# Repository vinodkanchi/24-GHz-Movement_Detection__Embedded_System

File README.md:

# 24-GHz-Movement_Detection__Embedded_System
The project is movement detection system where we design a PCB board for a Bandpass filter for allowing specific frequency using KiCad, then we do an embedded detection system using FreeSo-2, here we use ADC,DAC and LED's. Finally the next step is to test the model for the required frequency and gain measurements.

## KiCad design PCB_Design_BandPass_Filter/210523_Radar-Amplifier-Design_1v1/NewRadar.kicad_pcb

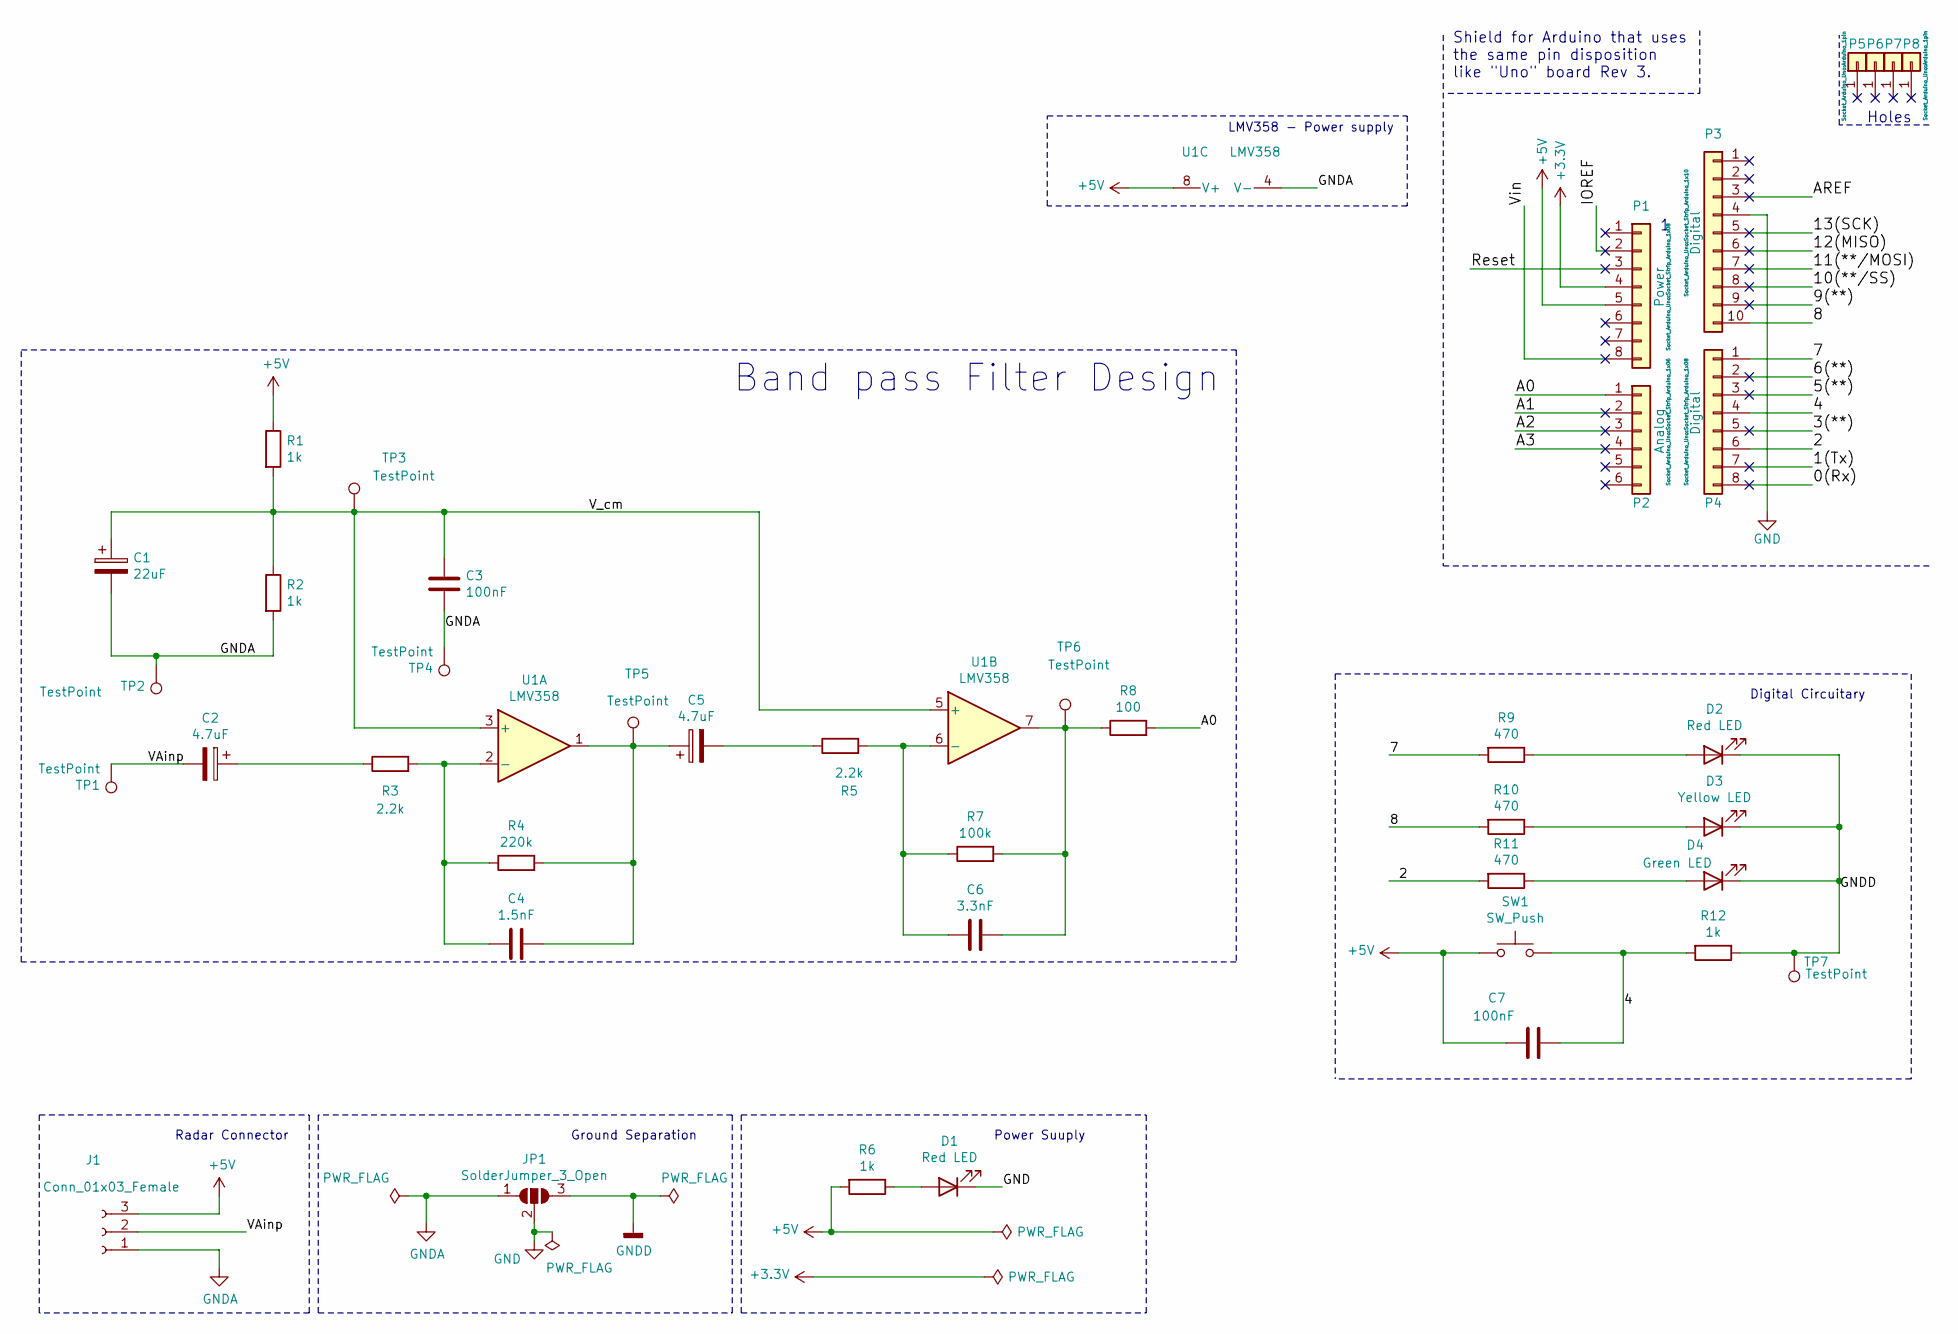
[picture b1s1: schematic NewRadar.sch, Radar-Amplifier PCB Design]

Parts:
C1: 22uF; C_Radial_D5.0mm_H11.0mm_P2.00mm
C2, C5: 4.7uF; C_Radial_D5.0mm_H11.0mm_P2.00mm
C3, C7: 100nF; C_Rect_L7.2mm_W2.5mm_P5.00mm_FKS2_FKP2_MKS2_MKP2
C4: 1.5nF; C_Rect_L7.2mm_W4.5mm_P5.00mm_FKS2_FKP2_MKS2_MKP2
C6: 3.3nF; C_Rect_L7.2mm_W4.5mm_P5.00mm_FKS2_FKP2_MKS2_MKP2
D1, D2: Red LED; LED_1206_3216Metric_Pad1.42x1.75mm_HandSolder
D3: Yellow LED; LED_1206_3216Metric_Pad1.42x1.75mm_HandSolder
D4: Green LED; LED_1206_3216Metric_Pad1.42x1.75mm_HandSolder
J1: Conn_01x03_Female; PinSocket_1x03_P2.54mm_Horizontal
JP1: SolderJumper_3_Open; SolderJumper-3_P1.3mm_Open_RoundedPad1.0x1.5mm_NumberLabels
P1: Power; Socket_Strip_Arduino_1x08
P2: Analog; Socket_Strip_Arduino_1x06
P3: Digital; Socket_Strip_Arduino_1x10
P4: Digital; Socket_Strip_Arduino_1x08
P5, P6, P7, P8: CONN_01X01; Arduino_1pin
R1, R2: 1k; R_Axial_DIN0207_L6.3mm_D2.5mm_P10.16mm_Horizontal
R3, R5: 2.2k; R_Axial_DIN0207_L6.3mm_D2.5mm_P10.16mm_Horizontal
R4: 220k; R_Axial_DIN0207_L6.3mm_D2.5mm_P10.16mm_Horizontal
R6, R12: 1k; R_1206_3216Metric_Pad1.30x1.75mm_HandSolder
R7: 100k; R_Axial_DIN0207_L6.3mm_D2.5mm_P10.16mm_Horizontal
R8: 100; R_Axial_DIN0207_L6.3mm_D2.5mm_P10.16mm_Horizontal
R9, R10, R11: 470; R_1206_3216Metric_Pad1.30x1.75mm_HandSolder
SW1: SW_Push; SW_PUSH_6mm_H7.3mm
TP1, TP2, TP3, TP4, TP5, TP6, TP7: TestPoint; Pin_D1.0mm_L10.0mm
U1: LMV358; DIP-8_W7.62mm_Socket

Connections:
+3V3: P1.4
+5V: C7.1, J1.3, P1.5, R1.1, R6.2, SW1.1, U1.8 (V+)
/0(Rx): P4.8
/1(Tx): P4.7
/2: P4.6, R11.2
/3(**): P4.5
/4: C7.2, P4.4, R12.2, SW1.2
/5(**): P4.3
/6(**): P4.2
/7: P4.1, R9.2
/8: P3.10, R10.2
/9(**): P3.9
/10(**/SS): P3.8
/11(**/MOSI): P3.7
/12(MISO): P3.6
/13(SCK): P3.5
/A0: P2.1, R8.2
/A1: P2.2
/A2: P2.3
/A3: P2.4
/AREF: P3.3
/IOREF: P1.2
/Reset: P1.3
/VAinp: C2.2, J1.2, TP1.1
/V_cm: C1.1, C3.1, R1.2, R2.1, TP3.1, U1.3 (+), U1.5 (+)
/Vin: P1.8
GND: D1.1 (K), JP1.2 (C), P3.4
GNDA: C1.2, C3.2, J1.1, JP1.1 (A), R2.2, TP2.1, TP4.1, U1.4 (V-)
GNDD: D2.1 (K), D3.1 (K), D4.1 (K), JP1.3 (B), R12.1, TP7.1
unnamed: C2.1, R3.1
unnamed: C4.1, C5.1, R4.2, TP5.1, U1.1
unnamed: C4.2, R3.2, R4.1, U1.2 (-)
unnamed: C5.2, R5.1
unnamed: C6.1, R7.2, R8.1, TP6.1, U1.7
unnamed: C6.2, R5.2, R7.1, U1.6 (-)
unnamed: D1.2 (A), R6.1
unnamed: D2.2 (A), R9.1
unnamed: D3.2 (A), R10.1
unnamed: D4.2 (A), R11.1

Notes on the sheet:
Holes
Shield for Arduino that uses the same pin disposition like "Uno" board Rev 3.
Band pass Filter Design
LMV358 - Power supply
Digital Circuitary
Radar Connector
Ground Separation
Power Suuply

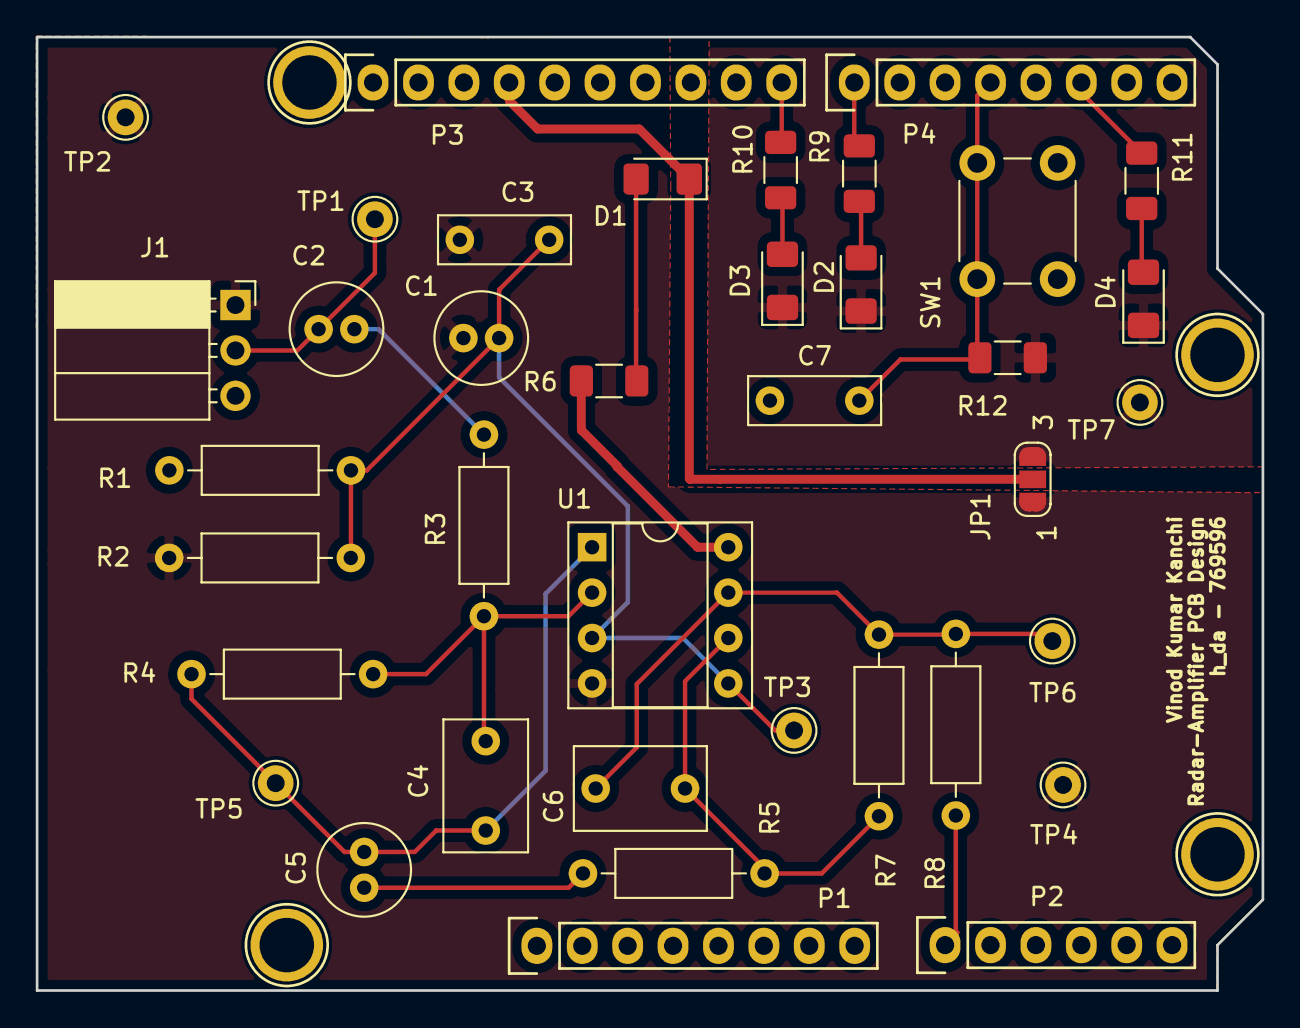
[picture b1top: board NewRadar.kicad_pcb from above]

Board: 4 copper layers, 68.6 x 53.3 mm, 42 parts (0 on the bottom side), 21 nets.

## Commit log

2021-08-31 Second Commit to add files
